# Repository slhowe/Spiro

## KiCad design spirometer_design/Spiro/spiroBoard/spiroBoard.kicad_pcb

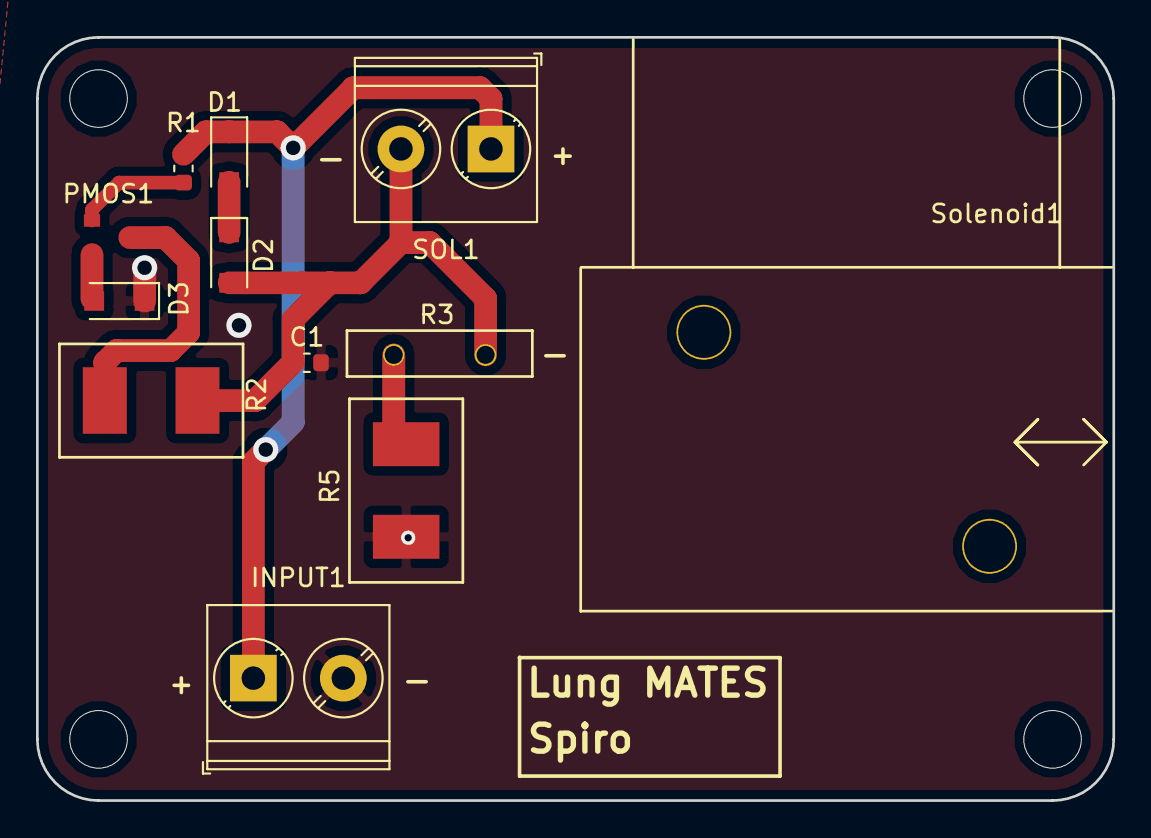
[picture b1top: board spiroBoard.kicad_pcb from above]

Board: 2 copper layers, 59.8 x 42.4 mm, 16 parts (0 on the bottom side), 8 nets.

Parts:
C1: 4.7mF; C_0603_1608Metric
D1, D2, D3: 3A 100V; D_SOD-123F
H1, H2, H3, H4: MountingHole; MountingHole_3.2mm_M3
INPUT1: Screw_Terminal_01x02; TerminalBlock_Phoenix_PT-1,5-2-5.0-H_1x02_P5.00mm_Horizontal
PMOS1: RQ5E035ATTCL; TSMT3-SC-96-PMOS
R1: 22; R_0603_1608Metric
R2: 22; Resistor 2512 (6432 Metric)
R3: 4.0; PWR221T-30-RESISTOR
R5: 0.43; Resistor 2512 (6432 Metric)
SOL1: Screw_Terminal_01x02; TerminalBlock_Phoenix_PT-1,5-2-5.0-H_1x02_P5.00mm_Horizontal
Solenoid1: 5VDC 8.2W 3.2Ohm; DSOL-0630-05E-SOLENOID

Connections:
/GND: C1.2, D3.1, INPUT1.2, R5.2
/Vin: D1.1, INPUT1.1, R1.1, SOL1.1
/solenoid-: C1.1, D2.2, R2.2, R3.1, SOL1.2
unnamed: D1.2, D2.1
unnamed: D3.2, PMOS1.2
unnamed: PMOS1.1, R1.2
unnamed: PMOS1.3, R2.1
unnamed: R3.2, R5.1

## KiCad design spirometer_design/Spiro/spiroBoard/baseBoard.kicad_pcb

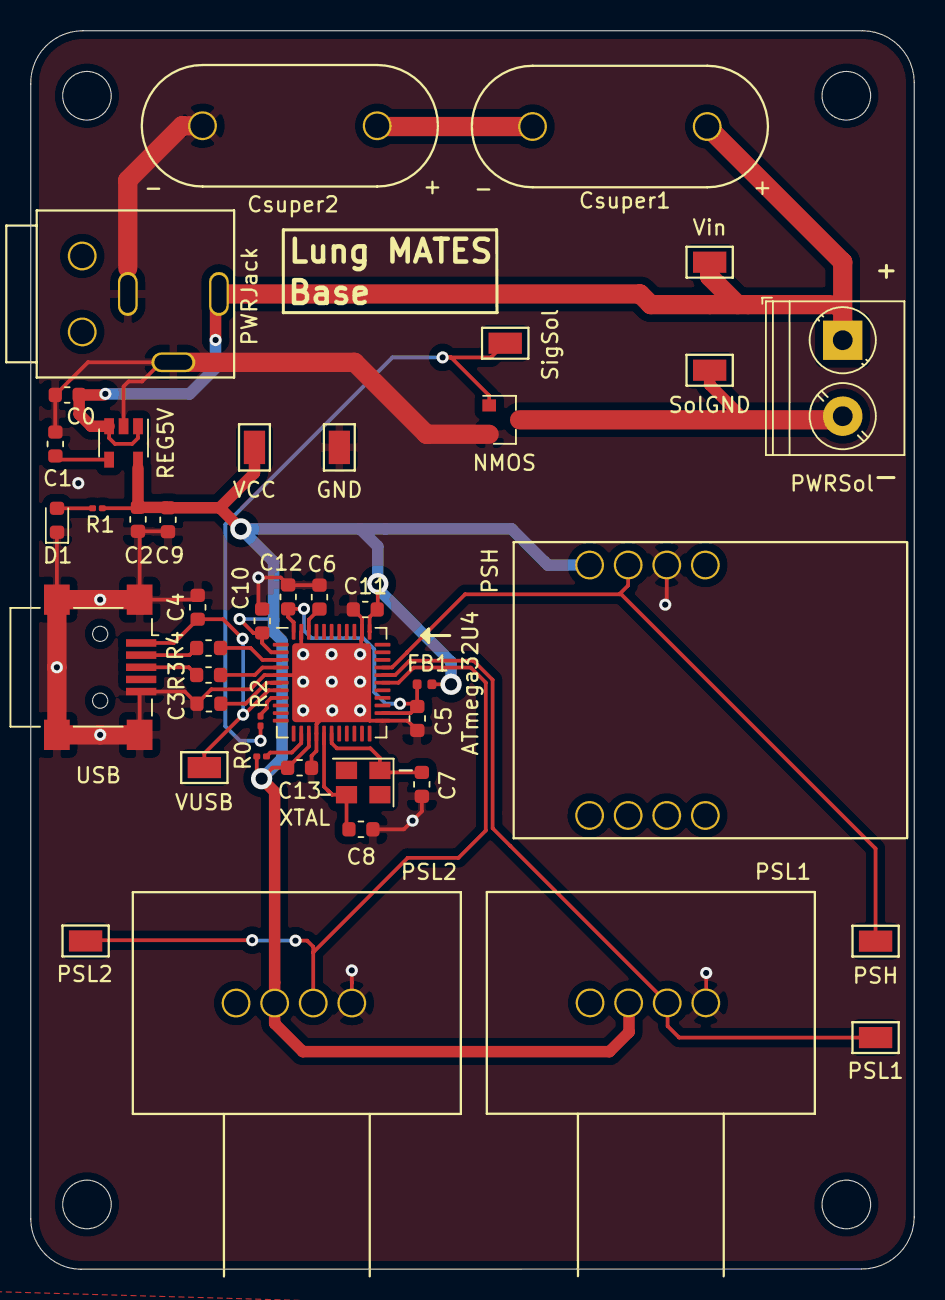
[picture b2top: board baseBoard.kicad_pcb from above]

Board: 2 copper layers, 58.2 x 81.5 mm, 46 parts (0 on the bottom side), 23 nets.

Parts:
ATmega32U4: ATmega32U4-MU; QFN-44-1EP_7x7mm_P0.5mm_EP5.2x5.2mm
C0, C3, C6: 1uF; C_0603_1608Metric
C1: 470pF; C_0603_1608Metric
C2: 2.2uF; C_0603_1608Metric
C4: 10uF; C_0603_1608Metric
C5: 100nF; C_0603_1608Metric
C7, C8: 22pF; C_0603_1608Metric
C9, C10, C11, C12, C13: 0.1uF; C_0603_1608Metric
Csuper1, Csuper2: 1F; SCMR18H105PRBB0-SuperCap1F
D1: LED; LED_0603_1608Metric
FB1: Ferrite_Bead; R_0402_1005Metric
GND: TestPoint; testPoint-2.2x1.4
H1, H2, H3, H4: MountingHole; MountingHole_3.2mm_M3
NMOS: 2N7002; SOT-23
PSH: ASDXRRX001PDAA5; ASDXRRX001PDAA5-PressureSensor
PSH#2: TestPoint; testPoint-2.2x1.4
PSL1, PSL2: SSCSNBN001NDAA5
PSL1#2, PSL2#2: TestPoint; testPoint-2.2x1.4
PWRJack: Barrel_Jack_Switch; PJ-025-powerJack
PWRSol: Screw_Terminal_01x02; TerminalBlock_Phoenix_PT-1,5-2-5.0-H_1x02_P5.00mm_Horizontal
R0, R1, R2: 1K; R_0201_0603Metric
R3, R4: 22; R_0603_1608Metric
REG5V: MIC5219YM5; SOT-23-5
SigSol: TestPoint; testPoint-2.2x1.4
SolGND: TestPoint; testPoint-2.2x1.4
USB: USB_B_Mini; USB_Mini-B_Lumberg_2486_01_Horizontal
VCC: TestPoint; testPoint-2.2x1.4
VUSB: TestPoint; testPoint-2.2x1.4
Vin: TestPoint; testPoint-2.2x1.4
XTAL: 16MHz; Crystal_SMD_SeikoEpson_TSX3225-4Pin_3.2x2.5mm

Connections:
/AREF: ATmega32U4.42, C6.1
/AVCC: ATmega32U4.24, ATmega32U4.44, C5.1, C12.1, FB1.2
/D+: ATmega32U4.4, R3.1
/D-: ATmega32U4.3, R4.2
/PressureSensorHigh: ATmega32U4.30, PSH.2, PSH#2.1
/PressureSensorLow1: ATmega32U4.29, PSL1.3, PSL1#2.1
/PressureSensorLow2: ATmega32U4.28, PSL2.3, PSL2#2.1
/VCC: ATmega32U4.2, ATmega32U4.14, ATmega32U4.34, C2.1, C9.1, C10.1, C11.1, C13.1, FB1.1, PSH.1, PSL1.2, PSL2.2, R0.2, R1.2, REG5V.5, VCC.1
/VUSB: ATmega32U4.7, C4.1, USB.1, VUSB.1
/Vin: C0.1, Csuper1.1, PWRJack.1, PWRSol.1, REG5V.1, REG5V.3, Vin.1
/solenoidGND: NMOS.3, PWRSol.2, SolGND.1
/solenoidToggle: ATmega32U4.8, R2.2
GND: ATmega32U4.5, ATmega32U4.15, ATmega32U4.23, ATmega32U4.35, ATmega32U4.43, ATmega32U4.45, C0.2, C1.2, C2.2, C3.2, C4.2, C5.2, C6.2, C7.1, C8.2, C9.2, C10.2, C11.2, C12.2, C13.2, Csuper2.2, D1.1, GND.1, NMOS.2, PSH.3, PSL1.4, PSL2.4, PWRJack.2, PWRJack.3, REG5V.2, USB.5, USB.6
unnamed: C1.1, REG5V.4
unnamed: ATmega32U4.6, C3.1
unnamed: ATmega32U4.17, C7.2, XTAL.1
unnamed: ATmega32U4.16, C8.1, XTAL.2
unnamed: Csuper1.2, Csuper2.1
unnamed: D1.2, R1.1
unnamed: R4.1, USB.2
unnamed: R3.2, USB.3
unnamed: NMOS.1, R2.1, SigSol.1
unnamed: ATmega32U4.13, R0.1

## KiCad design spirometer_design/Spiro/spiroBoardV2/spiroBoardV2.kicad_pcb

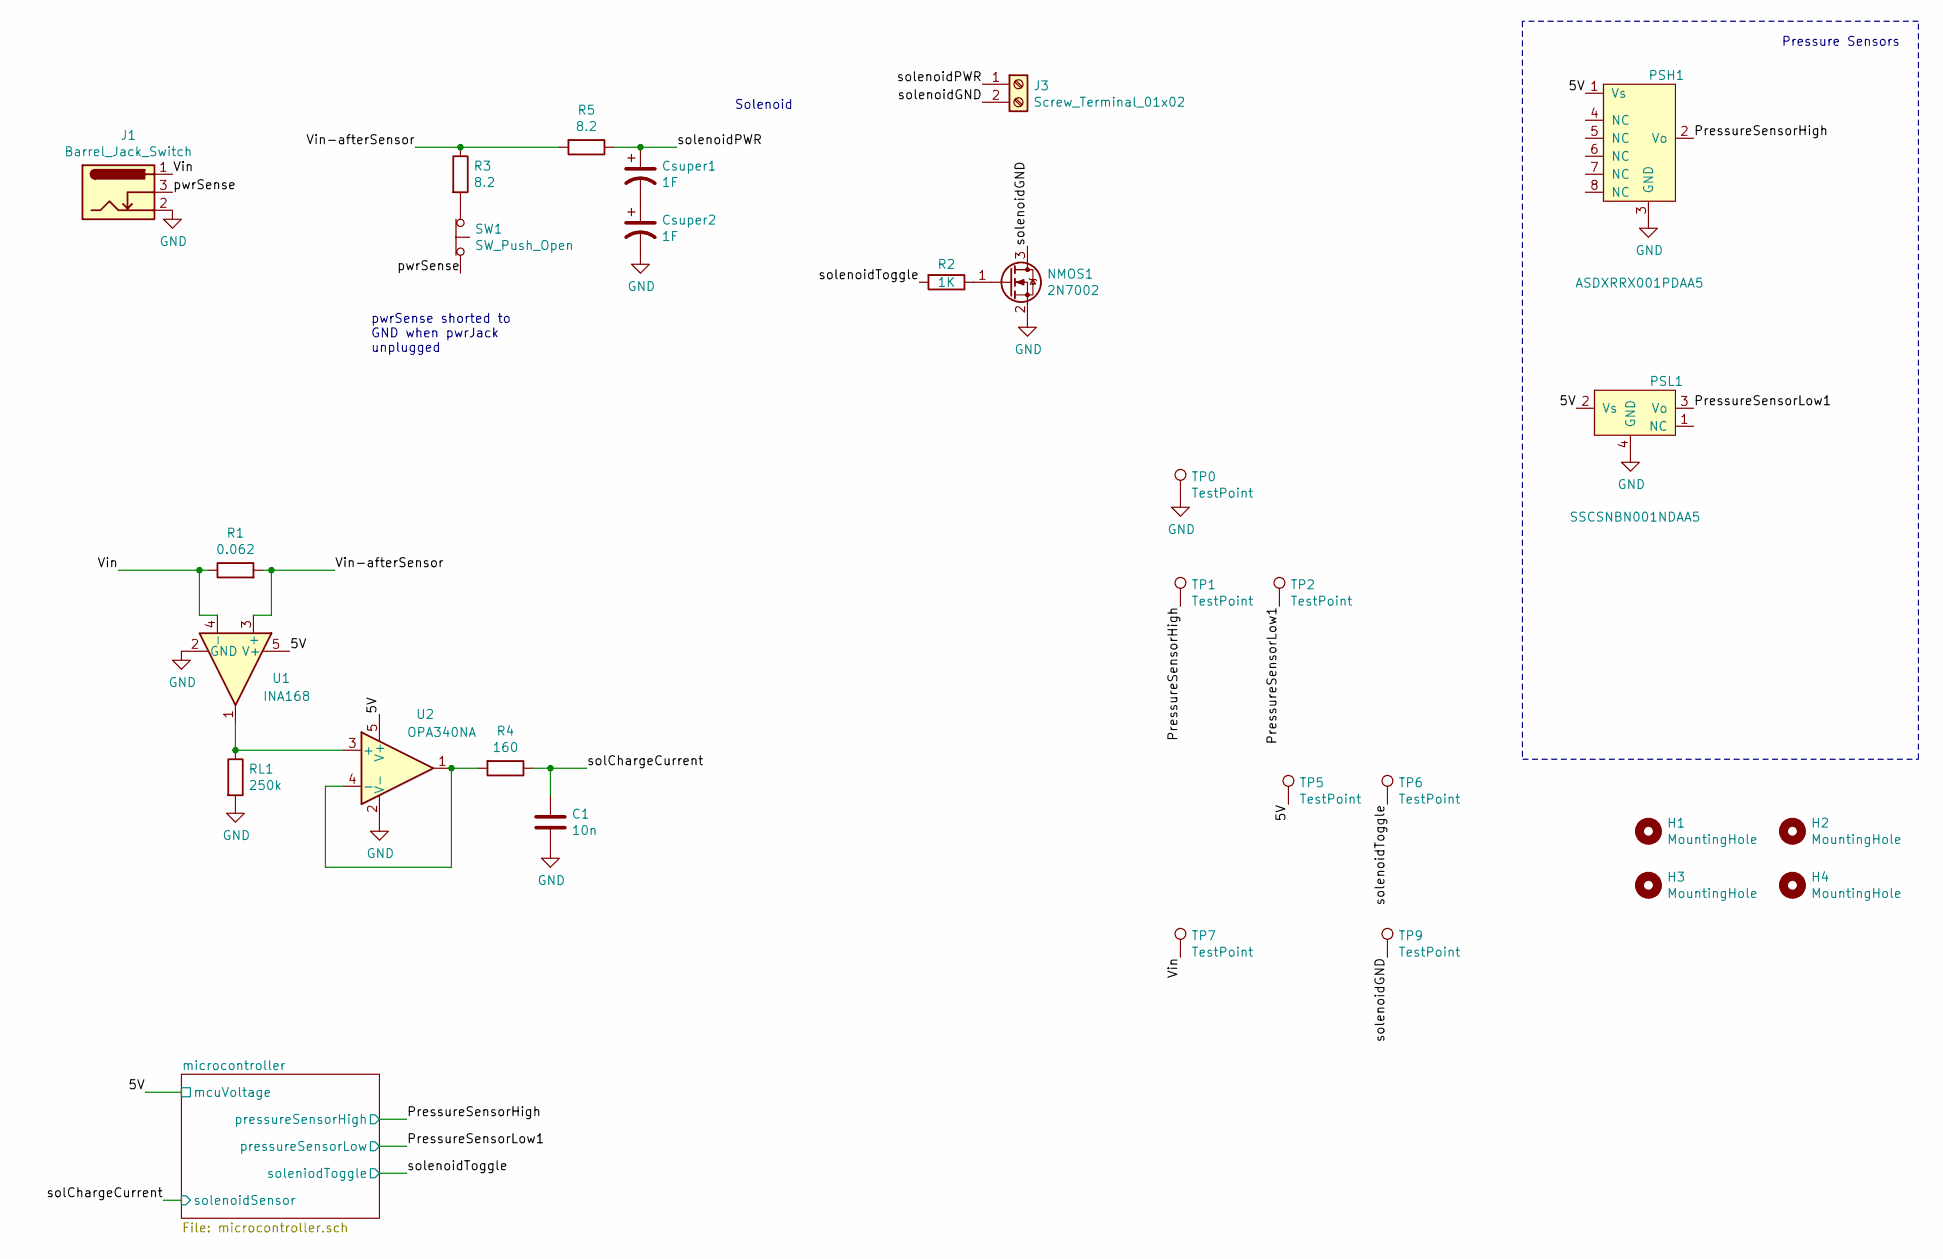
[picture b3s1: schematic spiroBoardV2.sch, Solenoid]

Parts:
C1: 10n; R_0603_1608Metric_Pad1.05x0.95mm_HandSolder
Csuper1, Csuper2: 1F; SCMR18H105PRBB0-SuperCap1F
H1, H2, H3, H4: MountingHole; MountingHole_3.2mm_M3
J1: Barrel_Jack_Switch; BarrelJack_Wuerth_6941xx301002
J3: Screw_Terminal_01x02; TerminalBlock_Phoenix_PT-1,5-2-5.0-H_1x02_P5.00mm_Horizontal
NMOS1: 2N7002; SOT-23
PSH1: ASDXRRX001PDAA5; ASDXRRX001PDAA5-PressureSensor
PSL1: SSCSNBN001NDAA5
R1: 0.062; R_1206_3216Metric_Pad1.42x1.75mm_HandSolder
R2: 1K; R_0603_1608Metric_Pad1.05x0.95mm_HandSolder
R3, R5: 8.2; TO-220-2_Vertical
R4: 160; R_1206_3216Metric_Pad1.42x1.75mm_HandSolder
RL1: 250k; R_0603_1608Metric_Pad1.05x0.95mm_HandSolder
SW1: SW_Push_Open; Slide_Switch_SPST_Through_Hole
TP0, TP1, TP2, TP5, TP6, TP7, TP9: TestPoint; testPoint-2.2x1.4
U1: INA168; SOT-23-5
U2: OPA340NA; SOT-23-5

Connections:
/5V: PSH1.1 (Vs), PSL1.2 (Vs), TP5.1, U1.5 (V+), U2.5 (V+); also elsewhere on the board
/PressureSensorHigh: PSH1.2 (Vo), TP1.1; also elsewhere on the board
/PressureSensorLow1: PSL1.3 (Vo), TP2.1; also elsewhere on the board
/Vin: J1.1, R1.1, TP7.1, U1.4 (-)
/Vin-afterSensor: R1.2, R3.1, R5.2, U1.3 (+)
/pwrSense: J1.3, SW1.2 (B)
/solChargeCurrent: C1.1, R4.1; also elsewhere on the board
/solenoidGND: J3.2, NMOS1.3 (D), TP9.1
/solenoidPWR: Csuper1.1, J3.1, R5.1
/solenoidToggle: R2.2, TP6.1; also elsewhere on the board
GND: C1.2, Csuper2.2, J1.2, NMOS1.2 (S), PSH1.3 (GND), PSL1.4 (GND), RL1.2, TP0.1, U1.2 (GND), U2.2 (V-); also elsewhere on the board
unnamed: Csuper1.2, Csuper2.1
unnamed: NMOS1.1 (G), R2.1
unnamed: R3.2, SW1.1 (A)
unnamed: R4.2, U2.1, U2.4 (-)
unnamed: RL1.1, U1.1, U2.3 (+)

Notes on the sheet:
Pressure Sensors
Solenoid
pwrSense shorted to GND when pwrJack unplugged

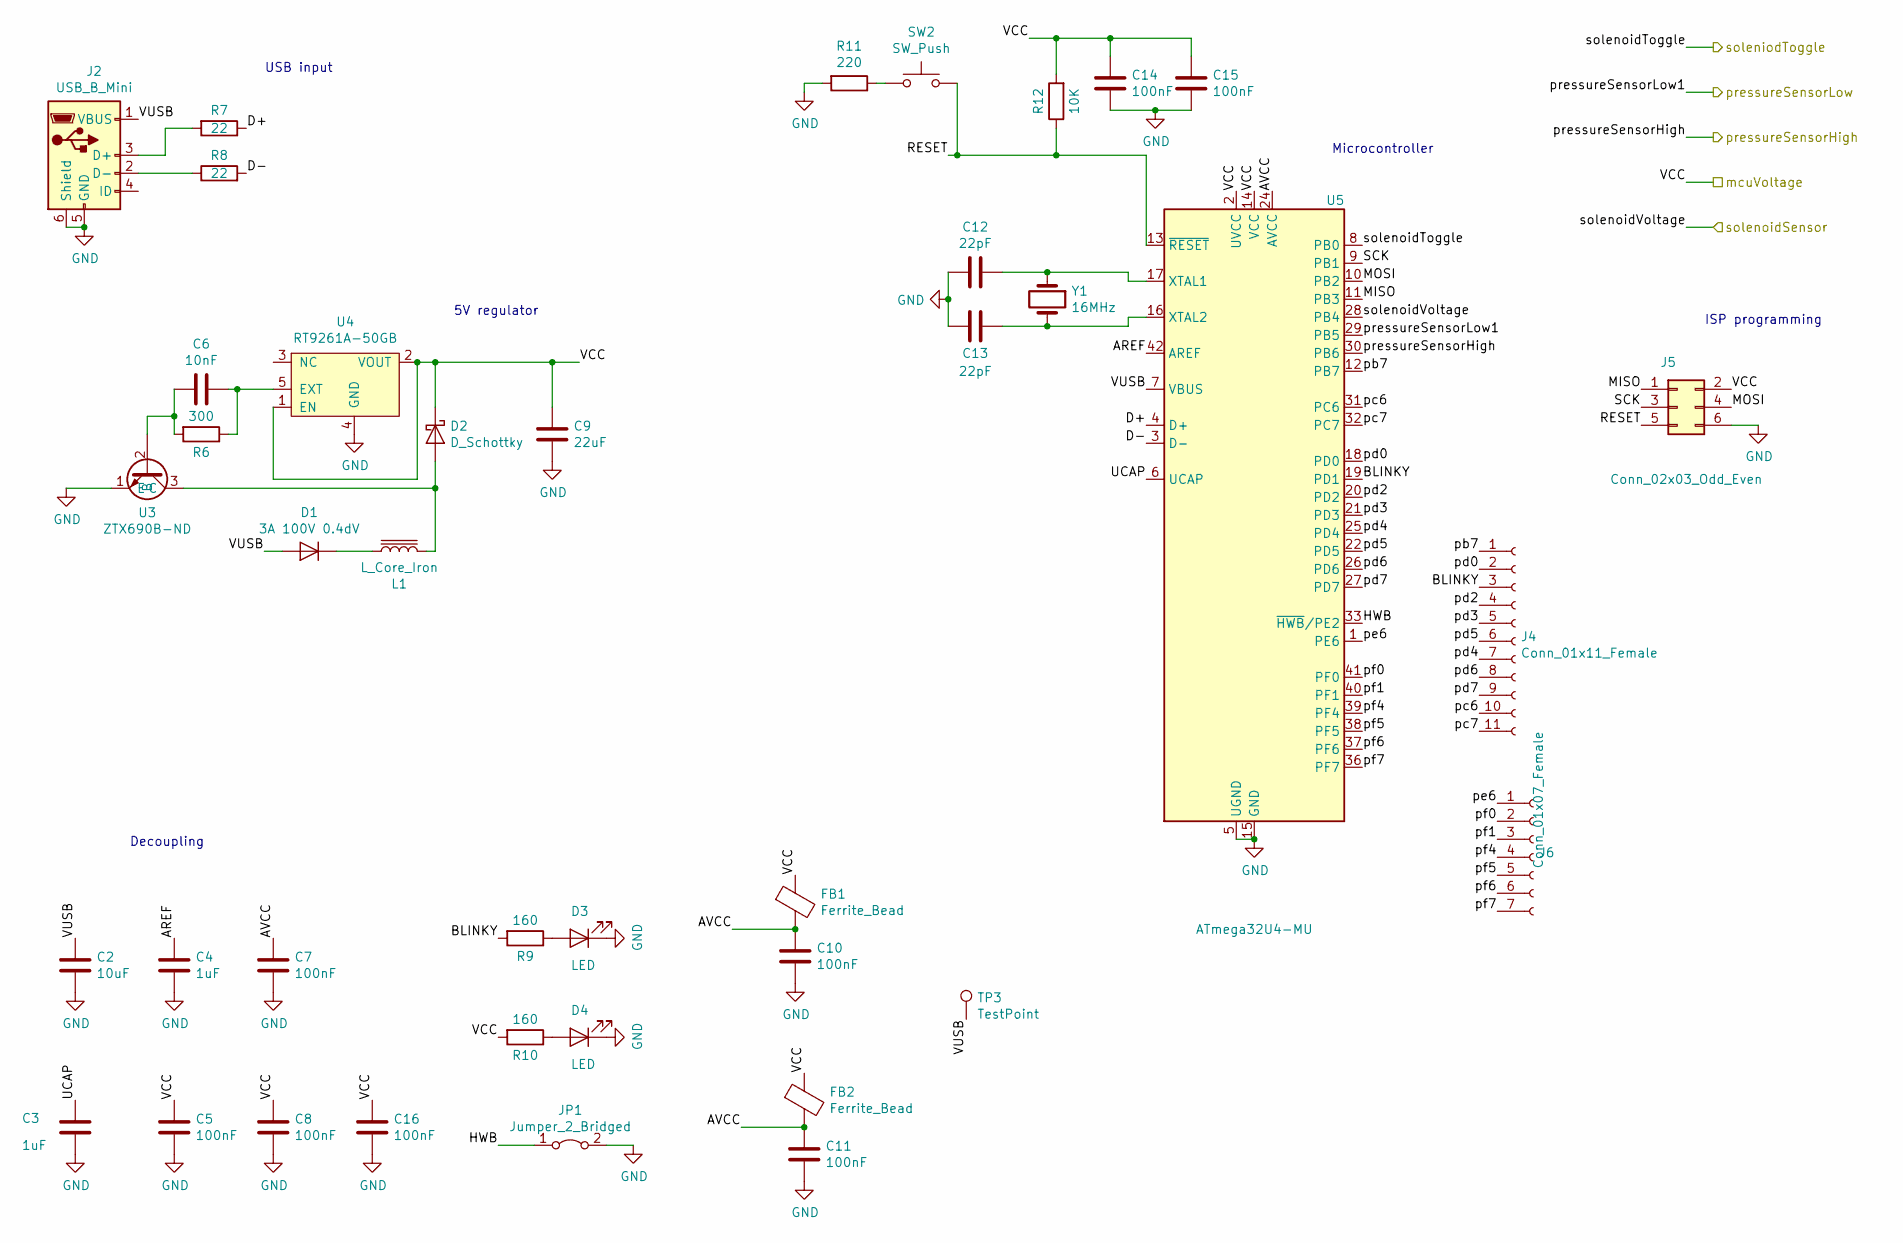
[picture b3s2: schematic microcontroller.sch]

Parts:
C2: 10uF; C_0603_1608Metric
C3, C4: 1uF; C_0603_1608Metric
C5, C7, C8, C10, C11, C14, C15, C16: 100nF; C_0603_1608Metric
C6: 10nF; R_0603_1608Metric_Pad1.05x0.95mm_HandSolder
C9: 22uF; R_0603_1608Metric_Pad1.05x0.95mm_HandSolder
C12, C13: 22pF; C_0603_1608Metric
D1: 3A 100V 0.4dV; D_SOD-123F
D2: D_Schottky; D_SOD-123
D3, D4: LED; LED_0603_1608Metric
FB1, FB2: Ferrite_Bead; R_0402_1005Metric
J2: USB_B_Mini; USB_Mini-B_Lumberg_2486_01_Horizontal
J4: Conn_01x11_Female; PinHeader_1x11_P2.54mm_Vertical
J5: Conn_02x03_Odd_Even; PinHeader_2x03_P2.54mm_Vertical
J6: Conn_01x07_Female; PinHeader_1x07_P2.54mm_Vertical
JP1: Jumper_2_Bridged; SolderJumper-2_P1.3mm_Bridged_Pad1.0x1.5mm
L1: L_Core_Iron; PA4334.273NLT
R6: 300; R_0603_1608Metric_Pad1.05x0.95mm_HandSolder
R7, R8: 22; R_0603_1608Metric
R9, R10: 160; R_0603_1608Metric_Pad1.05x0.95mm_HandSolder
R11: 220; R_0603_1608Metric_Pad1.05x0.95mm_HandSolder
R12: 10K; R_0603_1608Metric_Pad1.05x0.95mm_HandSolder
SW2: SW_Push; Switch_Tactile_SMD_6x6mm_PTS645
TP3: TestPoint; testPoint-2.2x1.4
U3: ZTX690B-ND; TO-92L_Inline
U4: RT9261A-50GB; SOT-23-5_HandSoldering
U5: ATmega32U4-MU; QFN-44-1EP_7x7mm_P0.5mm_EP5.2x5.2mm
Y1: 16MHz; Crystal_SMD_SeikoEpson_TSX3225-4Pin_3.2x2.5mm

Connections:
/5V: C5.1, C8.1, C9.1, C14.1, C15.1, C16.1, D2.1 (K), FB1.1, FB2.1, J5.2, R10.2, R12.2, U4.1 (EN), U4.2 (VOUT), U5.2 (UVCC), U5.14 (VCC), U5.34 (VCC); also elsewhere on the board
/PressureSensorHigh: U5.30 (PB6); also elsewhere on the board
/PressureSensorLow1: U5.29 (PB5); also elsewhere on the board
/microcontroller/AREF: C4.1, U5.42 (AREF)
/microcontroller/AVCC: C7.1, C10.1, C11.1, FB1.2, FB2.2, U5.24 (AVCC), U5.44 (AVCC)
/microcontroller/BLINKY: J4.3, R9.2, U5.19 (PD1)
/microcontroller/D+: R7.1, U5.4 (D+)
/microcontroller/D-: R8.2, U5.3 (D-)
/microcontroller/HWB: JP1.1 (A), U5.33 (~HWB~/PE2)
/microcontroller/MISO: J5.1, U5.11 (PB3)
/microcontroller/MOSI: J5.4, U5.10 (PB2)
/microcontroller/RESET: J5.5, R12.1, SW2.1, U5.13 (~RESET)
/microcontroller/SCK: J5.3, U5.9 (PB1)
/microcontroller/UCAP: C3.1, U5.6 (UCAP)
/microcontroller/VUSB: C2.1, D1.2 (A), J2.1 (VBUS), TP3.1, U5.7 (VBUS)
/microcontroller/pb7: J4.1, U5.12 (PB7)
/microcontroller/pc6: J4.10, U5.31 (PC6)
/microcontroller/pc7: J4.11, U5.32 (PC7)
/microcontroller/pd0: J4.2, U5.18 (PD0)
/microcontroller/pd2: J4.4, U5.20 (PD2)
/microcontroller/pd3: J4.5, U5.21 (PD3)
/microcontroller/pd4: J4.7, U5.25 (PD4)
/microcontroller/pd5: J4.6, U5.22 (PD5)
/microcontroller/pd6: J4.8, U5.26 (PD6)
/microcontroller/pd7: J4.9, U5.27 (PD7)
/microcontroller/pe6: J6.1, U5.1 (PE6)
/microcontroller/pf0: J6.2, U5.41 (PF0)
/microcontroller/pf1: J6.3, U5.40 (PF1)
/microcontroller/pf4: J6.4, U5.39 (PF4)
/microcontroller/pf5: J6.5, U5.38 (PF5)
/microcontroller/pf6: J6.6, U5.37 (PF6)
/microcontroller/pf7: J6.7, U5.36 (PF7)
/solChargeCurrent: U5.28 (PB4); also elsewhere on the board
/solenoidToggle: U5.8 (PB0); also elsewhere on the board
GND: C2.2, C3.2, C4.2, C5.2, C7.2, C8.2, C9.2, C10.2, C11.2, C12.1, C13.2, C14.2, C15.2, C16.2, D3.1 (K), D4.1 (K), J2.5 (GND), J2.6 (Shield), J5.6, JP1.2 (B), R11.2, U3.1 (E), U4.4 (GND), U5.5 (UGND), U5.15 (GND), U5.23 (GND), U5.35 (GND), U5.43 (GND), U5.45 (GND); also elsewhere on the board
unnamed: C6.1, R6.1, U4.5 (EXT)
unnamed: C6.2, R6.2, U3.2 (B)
unnamed: C12.2, U5.17 (XTAL1), Y1.1
unnamed: C13.1, U5.16 (XTAL2), Y1.2
unnamed: D1.1 (K), L1.1
unnamed: D2.2 (A), L1.2, U3.3 (C)
unnamed: D3.2 (A), R9.1
unnamed: D4.2 (A), R10.1
unnamed: J2.2 (D-), R8.1
unnamed: J2.3 (D+), R7.2
unnamed: R11.1, SW2.2

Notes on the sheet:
Microcontroller
5V regulator
USB input
Decoupling
ISP programming

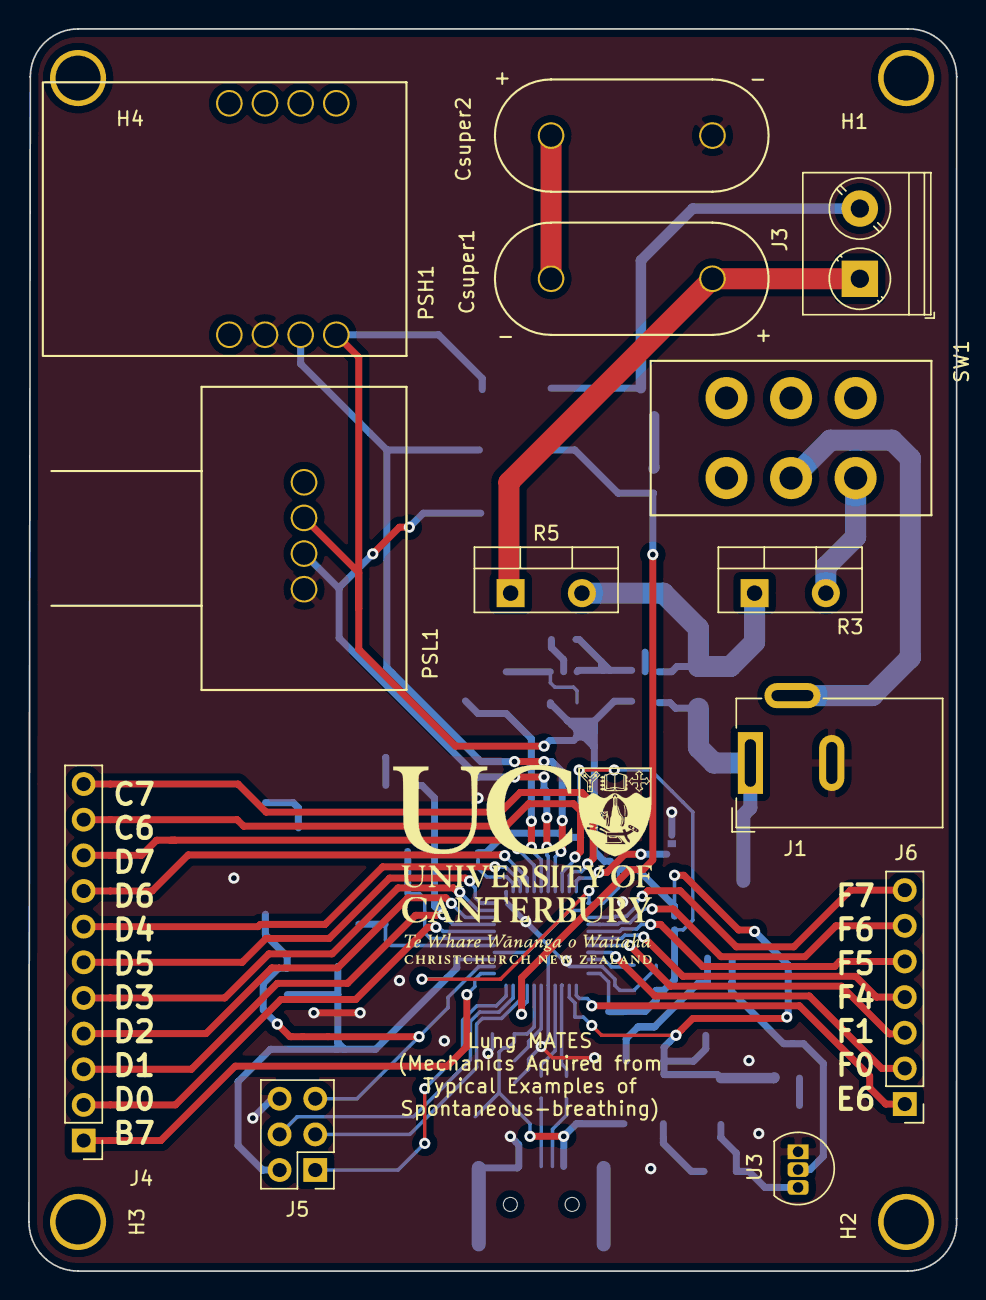
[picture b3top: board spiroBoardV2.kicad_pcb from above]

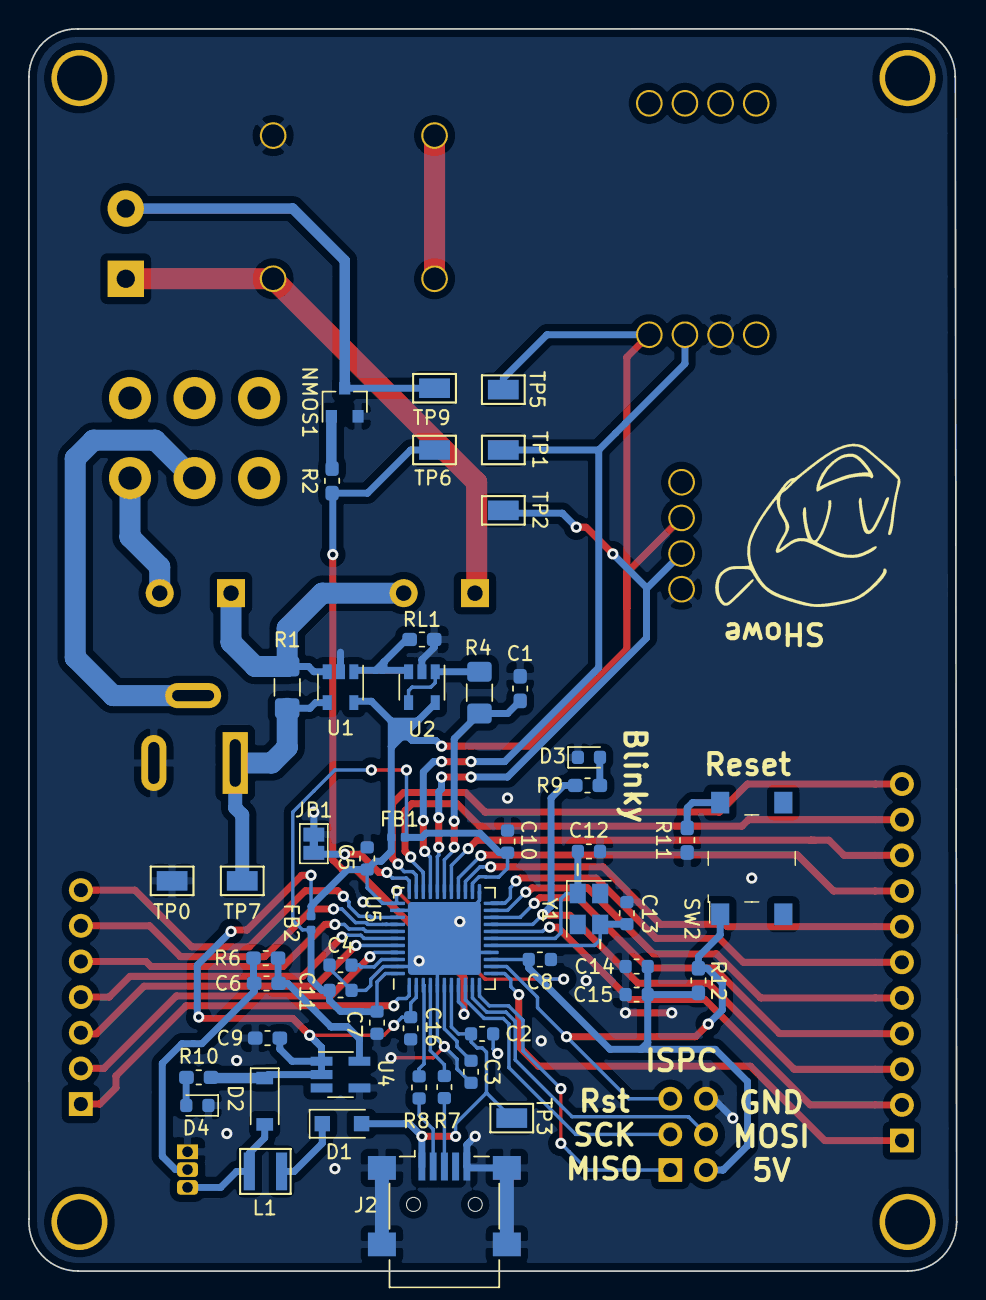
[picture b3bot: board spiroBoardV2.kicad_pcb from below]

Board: 2 copper layers, 66.1 x 88.5 mm, 68 parts (51 on the bottom side), 56 nets.

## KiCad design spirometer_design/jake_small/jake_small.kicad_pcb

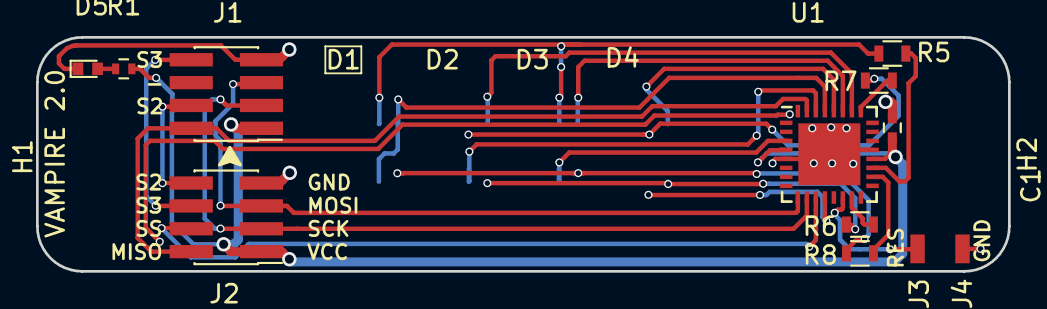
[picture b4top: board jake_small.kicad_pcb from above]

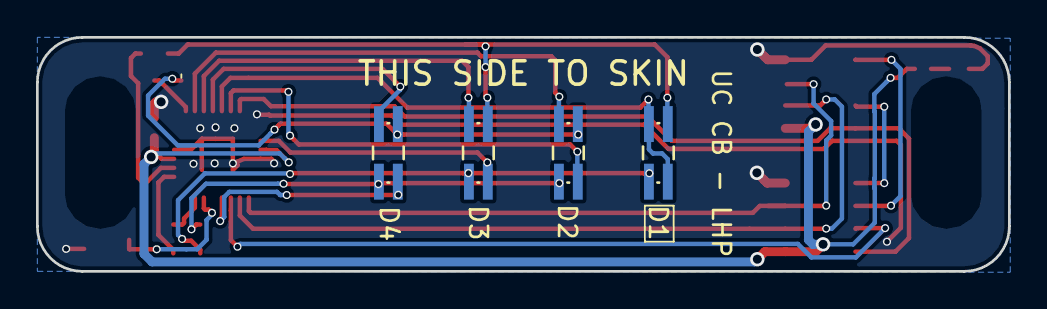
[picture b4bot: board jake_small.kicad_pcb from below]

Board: 2 copper layers, 54.0 x 13.0 mm, 18 parts (4 on the bottom side), 25 nets.

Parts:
C1: 100uF; C_0402
D1, D2, D3, D4: LED_Dual_CAAC; LED-4PIN-XZM2MRTNI55W
D5: LED; LED_0402
H1, H2: MountingHole; MountingHole-10x5-oval
J1, J2: Conn_01x08; Pin_Header_Straight_2x04_Pitch1.27mm_SMD
J3, J4: Conn_01x01; TP_1.6mmx0.8mm
R1: R; R_0402
R5, R7: 115R; R_0603
R6, R8: 70R; R_0603
U1: ATtiny167-MU; QFN-32-1EP_5x5mm_Pitch0.5mm

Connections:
/A_1: R6.1, U1.15
/A_1a: D2.2, D4.2, R7.2
/A_2: R8.1, U1.18
/A_2a: D1.2, D3.2, R5.2
/B_1: R5.1, U1.19
/B_1a: D1.3, D3.3, R8.2
/B_2: R7.1, U1.25
/B_2a: D2.3, D4.3, R6.2
/C1: D4.4, U1.28
/C2: D4.1, U1.12
/C3: D3.4, U1.27
/C4: D3.1, U1.3
/C5: D2.4, U1.26
/C6: D2.1, U1.30
/C7: D1.1, D1.4, U1.29
/MISO: J1.2, J2.2, U1.31
/MOSI: J1.5, J2.5, U1.9
/SCK: J1.3, J2.3, U1.10
/nRES: J3.1, U1.14
/nSS: J2.4, U1.11
/nSS1: J1.8, J2.6
/nSS3: J1.4, J2.8
GND: C1.2, D5.1, J1.7, J2.7, J4.1, U1.5, U1.21, U1.33
unnamed: D5.2, R1.1
VCC: C1.1, J1.1, J2.1, R1.2, U1.4, U1.20

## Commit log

2016-04-11 Have some data
2016-04-11 made a file for looking at data
2016-04-20 Fitting exponential decay to expiration - gives RC
2016-04-20 "Now fitting LSQ to a %age of flow drop"
2016-04-20 The model fit line extends all the way and looks pretty good See van drunen et al paper for more stuff
2016-04-21 Shifted the flow data as though a new resistance was added
2016-04-21 Looking at if a new resistence can be extracted, even if noisy
2016-04-22 Finding E and R for known starting R. Not sure of units for R - small R will make EoR huge
2016-04-22 error condition on first data point in filtering section
2016-04-22 New file made. Seeing if anything can be found from shifted pressure
2016-04-25 New function to split breaths
2016-04-26 Breaths now split into insp and exp indices
2016-04-26 split breath tuned to work for data sets 1 and 3
2016-04-26 breath splitter now tuned for loops and normal breaths for sets 1 & 3
2016-04-26 added function to check if starting points for breath are valid. Analysis function now checks if pairs are for the same breath
2016-04-26 Oops, had the greater and less than signs the wrong way around XD
2016-04-27 Section for splitting breaths is commented out. Trying fourier domain.
2016-04-29 e and r calc works with error for test case. Now looking at exp and insp
2016-05-02 elast calc seems to work but offset due to mass?
2016-08-18 Added new files
2016-08-18 old files removed
2016-09-22 Add hamming LP filter
2016-09-22 dump. need to commit more
2016-09-22 Add arduino code for spirometer
2016-09-22 Add differentiator code
2016-09-22 Add code for generating elastance from small data stepping
2016-09-22 Add example code
2016-09-22 Add code to read spirometer
2016-09-29 Add filtering to split breaths function
2016-10-09 fixed bugs in functions
2016-10-10 Estimation of pressure data from flow
2016-10-10 filtering data with hamming low pass filter
2016-10-10 Same as plotting script. Removed.
2016-10-10 plotting added to split breaths function
2016-10-10 Add function to find inflection points
2016-10-10 Remove some commented out code
2016-10-10 Add peak checking in inflection point detection. Now ignores small inflection points, focuses on large changes. Peak limit hard coded at 50, set to work for one test set
2016-10-10 Final inflection point at end of data
2016-10-11 Presure estimation as function. Need to try iteratively estimating pressure. Current estimation is ok but doesn.t capture small changes. Has large error in some places.
2016-10-12 Function to estimate pressure. Simple method, integrate on rising flow, constant on falling flow. Additional error fixing step after initial guess; it could be iterative?
2016-10-12 Better iteration. Has max error and iteration. Pressure change each iteration depends on the iteration number, more change for lower iterations
2016-10-17 Giving a big clean up
2016-10-18 Estimation is pretty good. Iteration is pretty bad
2016-10-18 Iteration number set to 0
2016-10-18 Rearranged and cleaned. Use factor*0.6 gives good-enough guess
2016-10-18 Add extensions to load pressure and flow data from .mat files
2016-10-18 Data extracted with extension functions
2016-10-19 sampling frequency as input to split breaths. Option to toggle data filtering in split breaths
2016-10-19 Now uses multiple datasets as input
2016-10-20 Comparison of variables at the bottom. Not very useful
2016-10-21 Save here. It is working nicely
2016-10-24 Pressure estimate and actual pressure now use different ranges as input
2016-10-25 Update how splits is plotted and increased filtering on splits
2016-10-25 extraction for PS/NAVA non-invasive data
2016-10-25 extraction for dated data type
2016-10-25 implemented data extraction for PS/NAVA non-invasive data and dated data
2016-10-25 Added in error check for when max volume is 0
2016-10-25 estimate_pressure cleaned up. stripped to minimum, using only volume as estimate
2016-10-25 Typo fix in estimate_pressure
2016-10-26 playing with gradients. Doesn't work because gradient specific for scaling fator
2016-10-30 Normalised correlation of R/E. Results suck.
2016-11-28 Stripped back to simple plotting case
2016-11-28 Giant dump of new/modified files, because I got lazy and didn't commit for ages
2016-12-01 Example of dynamic plotting and script that plots data from serial spirometer
2016-12-01 Checks if object altered since last read
2016-12-02 Starts of a plotting tool, with threading
2016-12-06 Plotting works but is very slow. Need to put plotting in thread? is CPU hogging
2016-12-06 Added a queue clearing function
2016-12-06 Plotting issue due to reading buffered serial at low frequency. Now plotting at rate set in breath_analyser, recording serial data at rate defined in serial_monitor. Max serial read frequency seems t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
2016-12-06 Forgot to commit this. Separated out plotting function into own class
2016-12-06 New threading class to analyse data
2016-12-06 Analyses expiration decay. Working for static data. Resistance found over spir + resistance by unplugging second pressure port, so always comparing to atmosphere
2016-12-07 analyser shell class now working. Currently only prints that it is alive
2016-12-08 Now plotting animation in gui in Wx_plotting using Tkinter. Analogue plotter: plotting frequency handled external to class.
2016-12-11 Plotting and not plotting now has same result in split_breaths
2017-04-26 need to update more
2017-04-26 really do
2017-09-13 modeling occlusions during tidal breathing
2018-02-26 always forget to commit...
2018-04-30 new for mask lpf
2018-05-18 first data
2018-05-18 update plotting to faster and only two presure channels
2018-05-18 decay analysis added
2018-06-20 dump again, starting office trial analysis
2018-06-25 added trial analysis
2018-06-25 changes Ps to Pm relationship finder for multiple datasets
2018-06-25 analysis plots data
2018-06-29 starting on correct Ps to Pm conversion
2018-07-12 resistance_calculation looking at higher range and data_analysis looking at high flow range for peak breaths
2019-08-28 shuttering
2019-09-09 looking at pressure changing
2019-09-19 fixed end target for linear fit
2019-09-23 Rename \ to lung-pump-decay
2019-10-16 New file. Improved data analysis for HFU trial
2020-03-15 germany
2020-03-16 fixed corr error and added p-values on output
2020-03-23 dump -- good luck
